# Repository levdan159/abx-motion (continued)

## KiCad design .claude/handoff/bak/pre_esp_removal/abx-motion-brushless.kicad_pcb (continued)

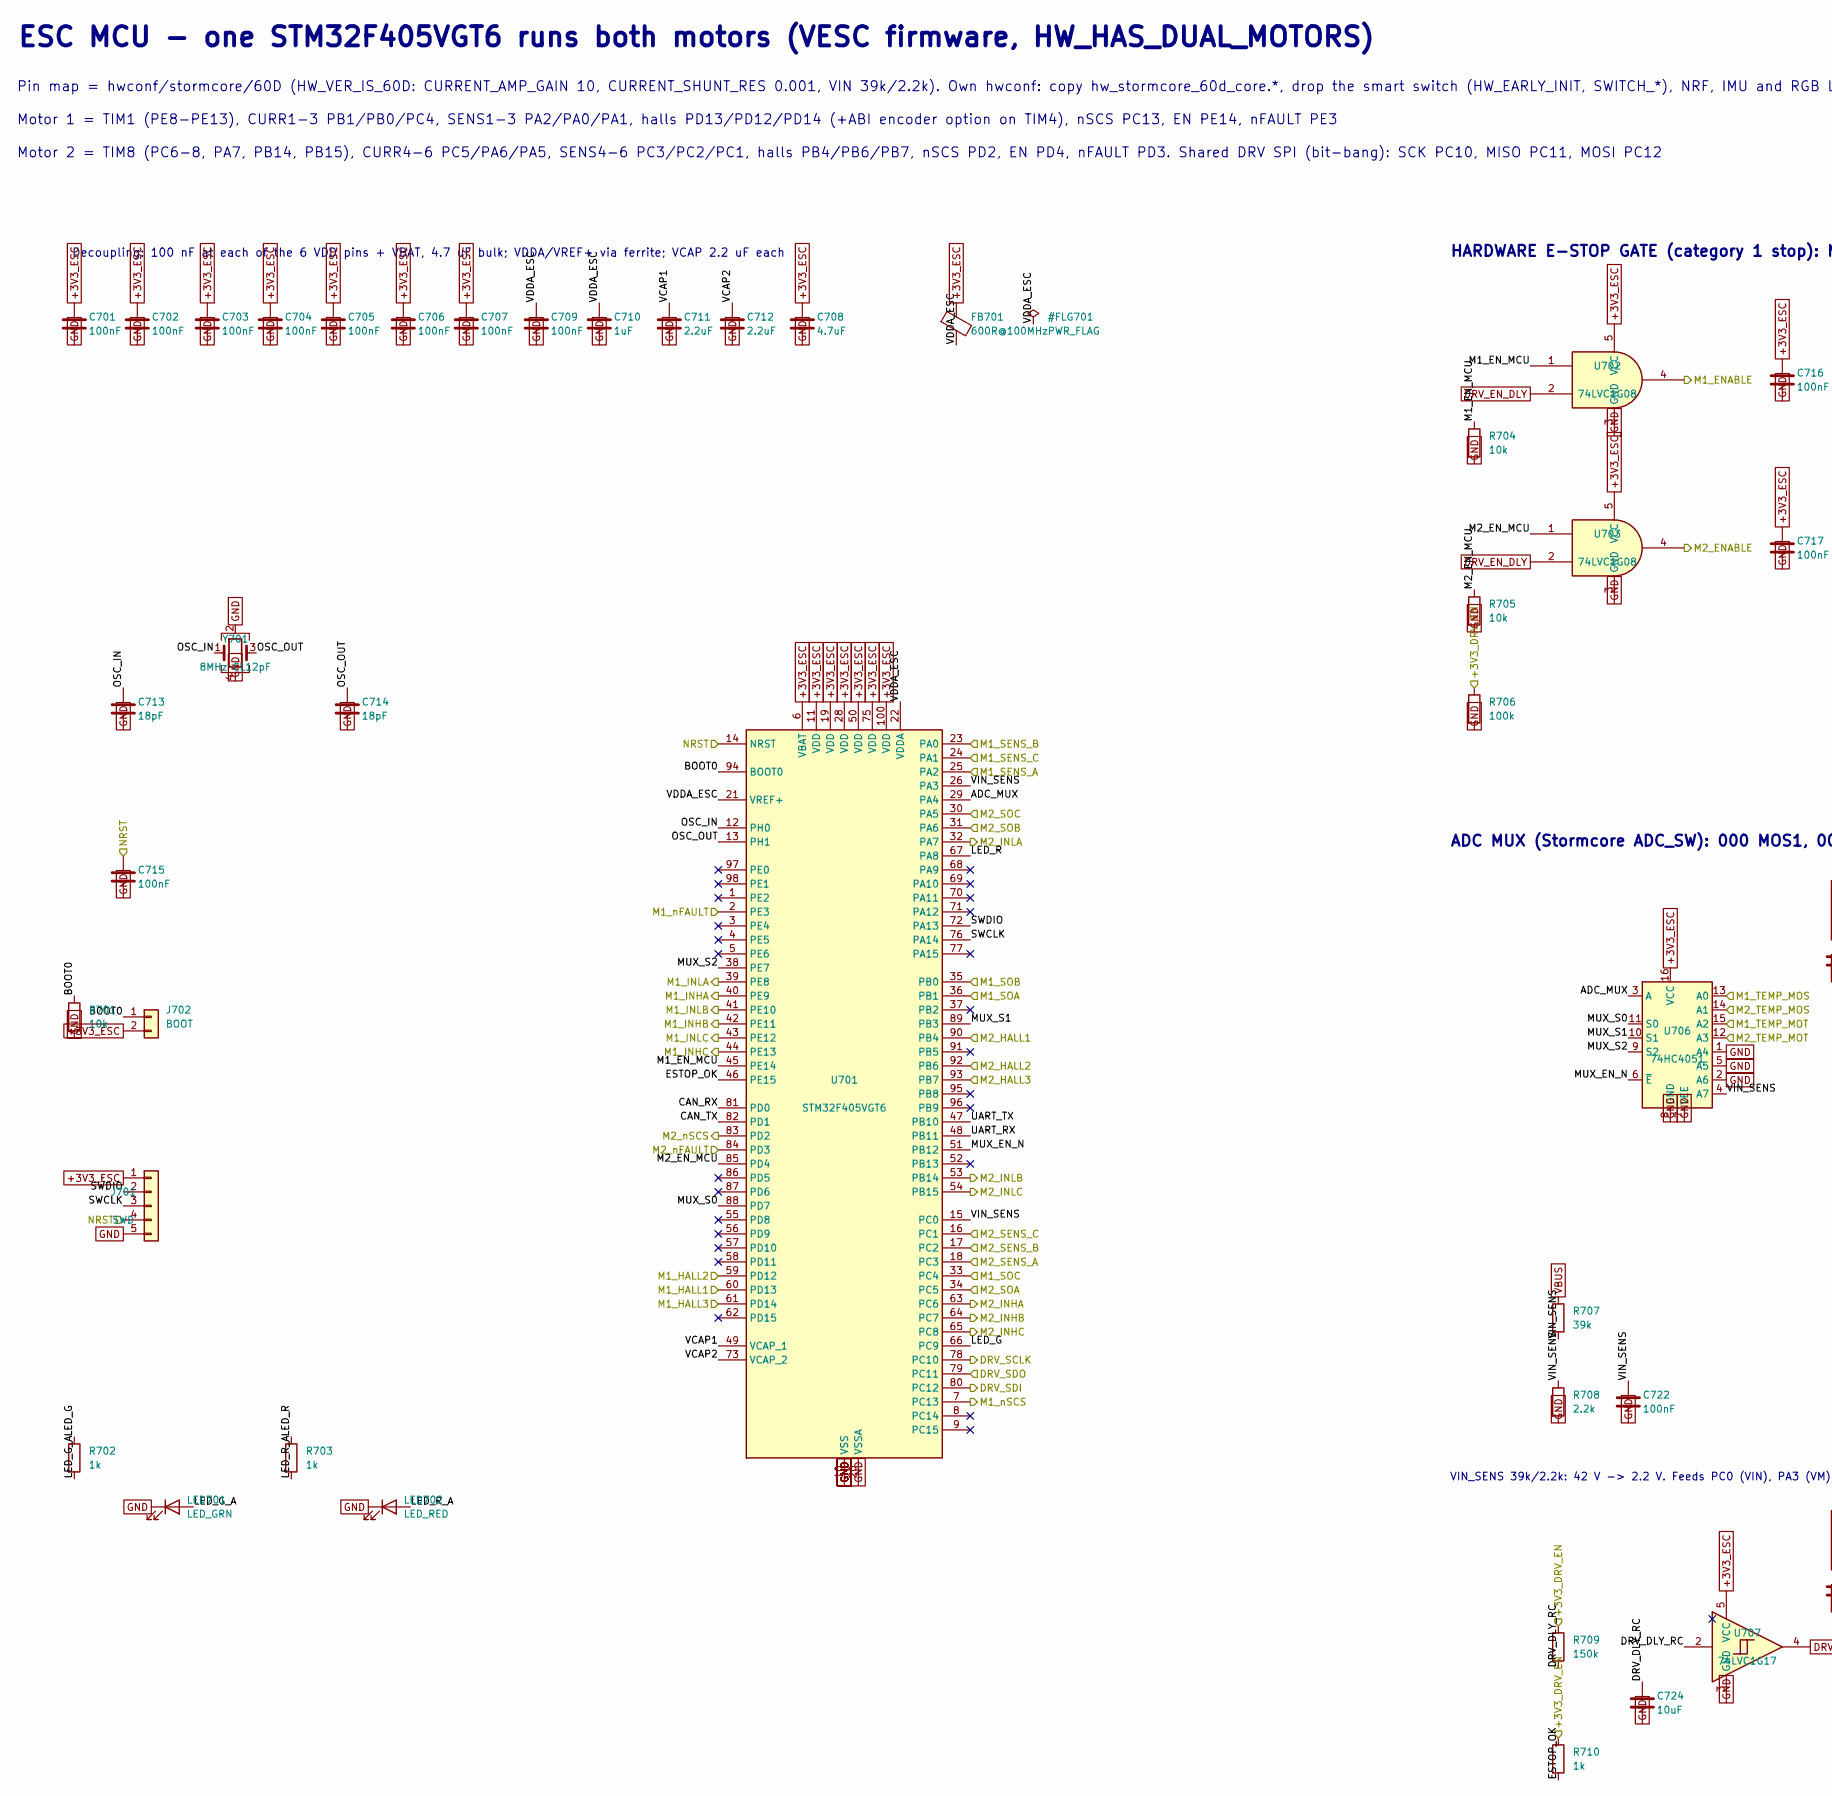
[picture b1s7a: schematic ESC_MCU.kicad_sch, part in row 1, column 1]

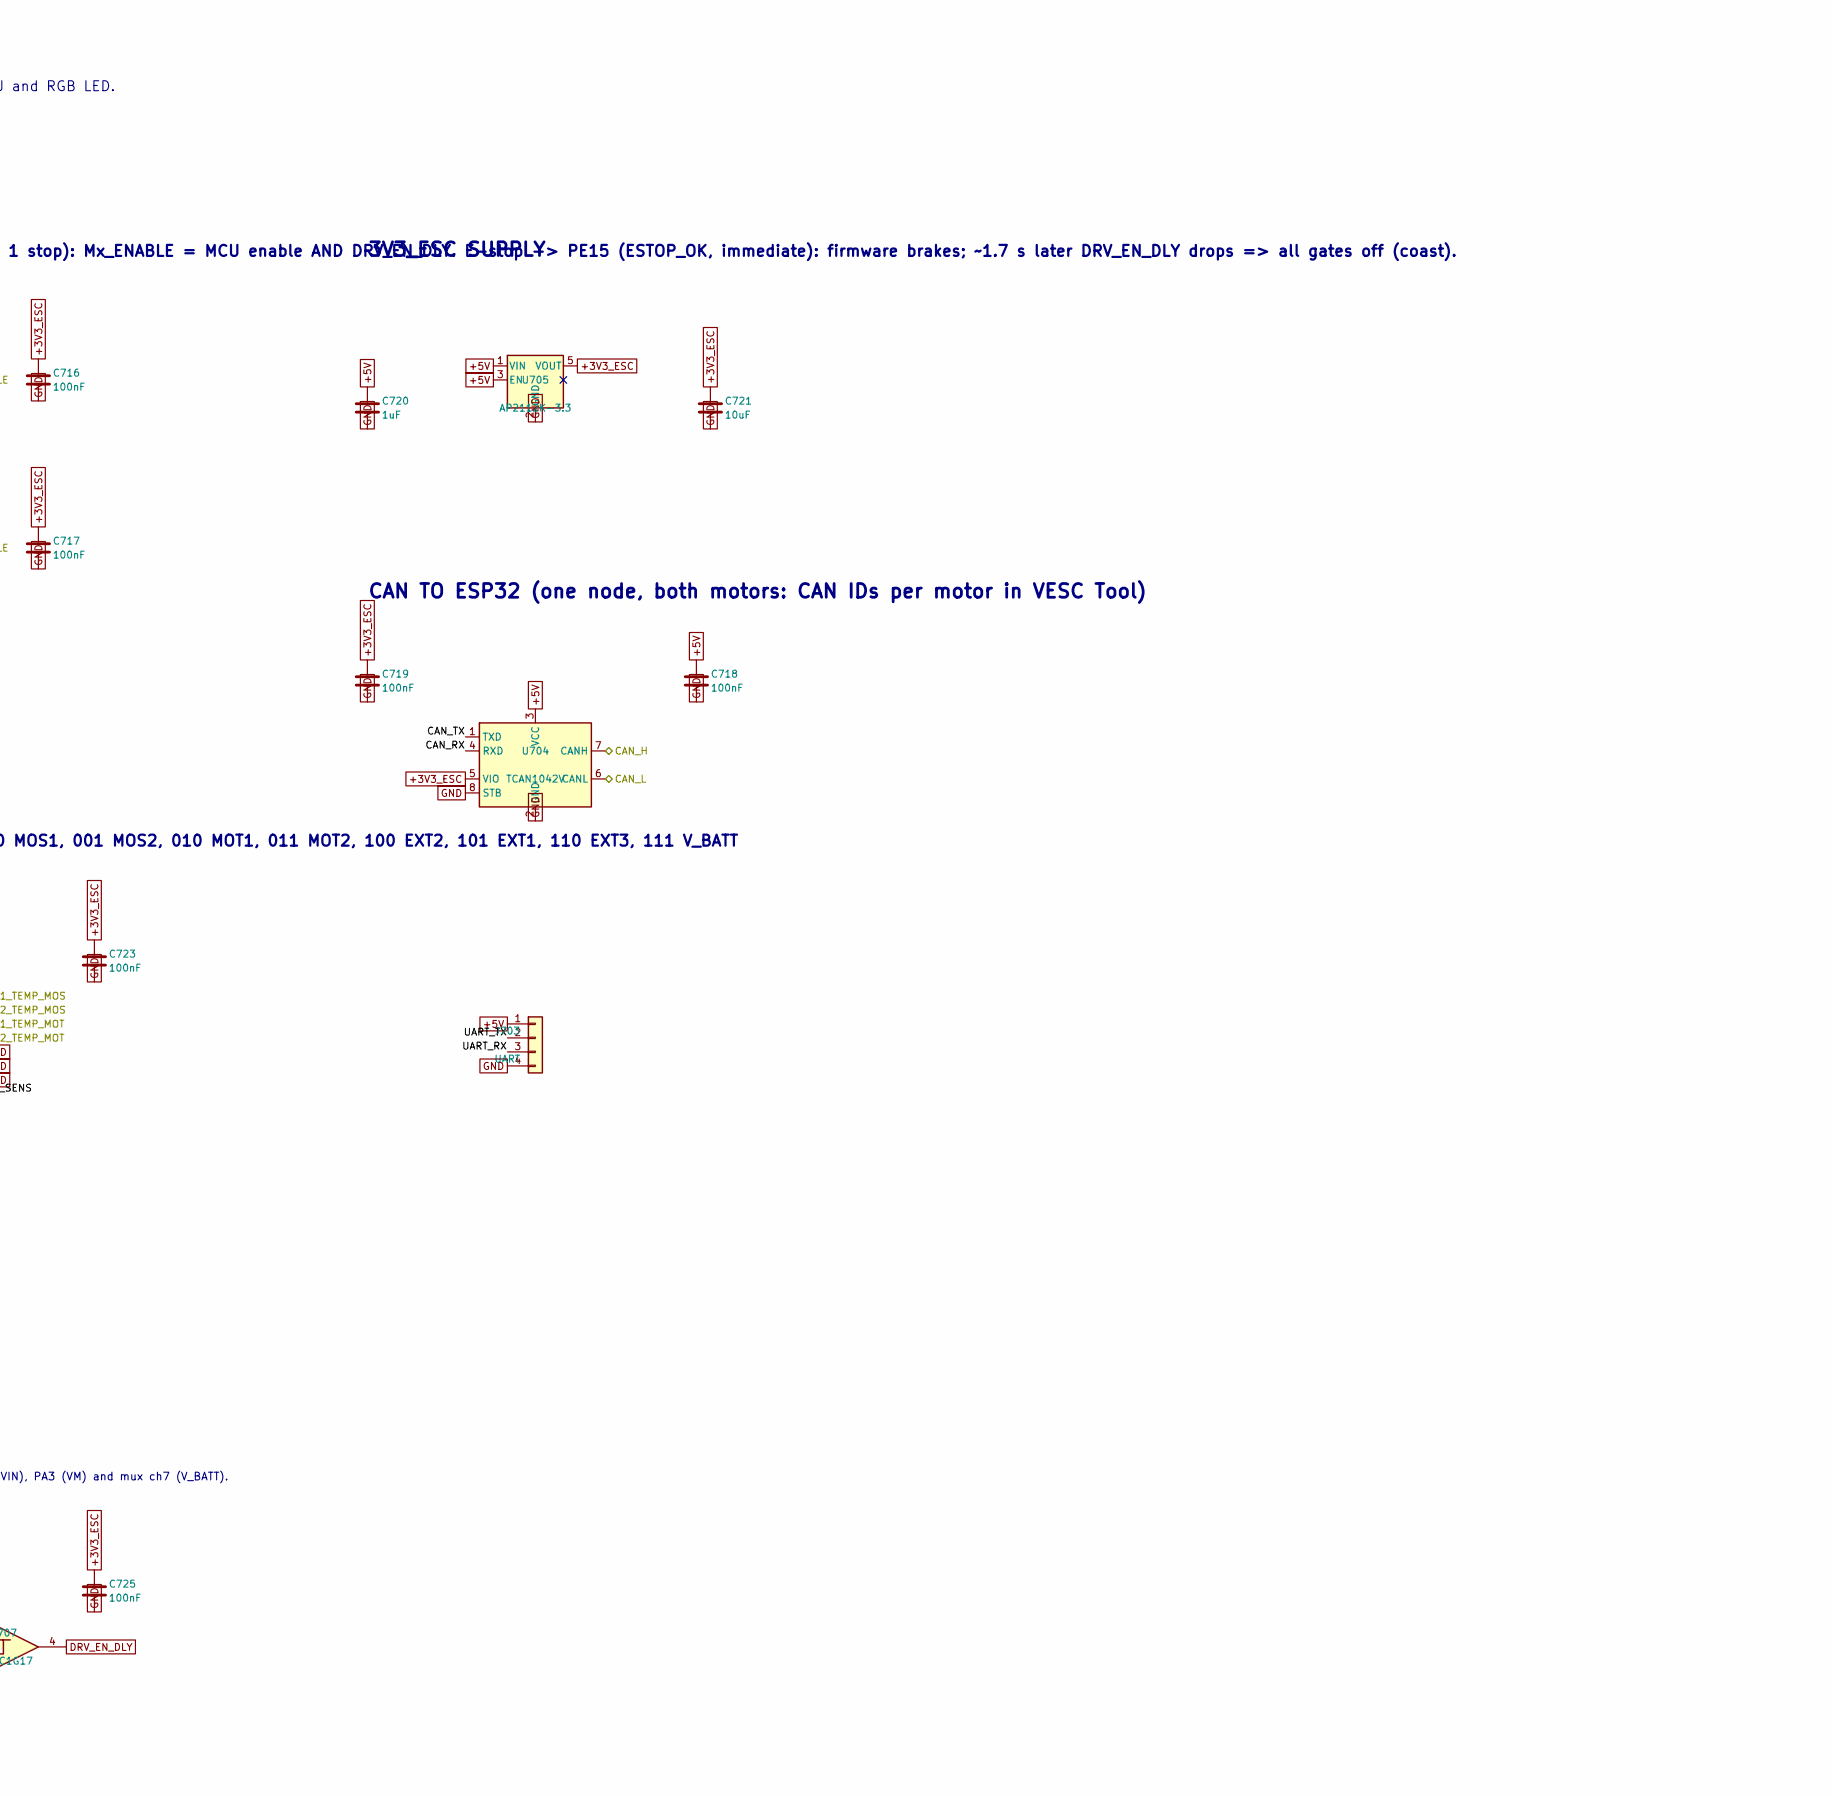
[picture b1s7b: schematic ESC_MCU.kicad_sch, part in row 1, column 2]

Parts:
C701, C702, C703, C704, C705, C706, C707, C709, C715, C716, C717, C718, C719, C722, C723, C725: 100nF; C_0603_1608Metric
C708: 4.7uF; C_0805_2012Metric
C710, C720: 1uF; C_0603_1608Metric
C711, C712: 2.2uF; C_0603_1608Metric
C713, C714: 18pF; C_0603_1608Metric
C721, C724: 10uF; C_0805_2012Metric
FB701: 600R@100MHz; L_0603_1608Metric
J701: SWD; PinHeader_1x05_P2.54mm_Vertical
J702: BOOT; PinHeader_1x02_P2.54mm_Vertical
J703: UART; JST_PH_B4B-PH-K_1x04_P2.00mm_Vertical
LED701: LED_GRN; LED_0603_1608Metric
LED702: LED_RED; LED_0603_1608Metric
R701, R704, R705: 10k; R_0603_1608Metric
R702, R703, R710: 1k; R_0603_1608Metric
R706: 100k; R_0603_1608Metric
R707: 39k; R_0805_2012Metric
R708: 2.2k; R_0603_1608Metric
R709: 150k; R_0603_1608Metric
U701: STM32F405VGT6; LQFP-100_14x14mm_P0.5mm
U702, U703: 74LVC1G08; SOT-23-5
U704: TCAN1042V; SOIC-8_3.9x4.9mm_P1.27mm
U705: AP2112K-3.3; SOT-23-5
U706: 74HC4051; TSSOP-16_4.4x5mm_P0.65mm
U707: 74LVC1G17; SOT-23-5
Y701: 8MHz CL12pF; Crystal_SMD_3225-4Pin_3.2x2.5mm

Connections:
+5V: C718.1, C720.1, J703.1, U704.3 (VCC), U705.1 (VIN), U705.3 (EN); also elsewhere on the board
/+3V3_DRV_EN: R706.1, R709.1, R710.1; also elsewhere on the board
/CAN_H: U704.7 (CANH); also elsewhere on the board
/CAN_L: U704.6 (CANL); also elsewhere on the board
/DRV_SCLK: U701.78 (PC10); also elsewhere on the board
/DRV_SDI: U701.80 (PC12); also elsewhere on the board
/DRV_SDO: U701.79 (PC11); also elsewhere on the board
/ESC_MCU/ADC_MUX: U701.29 (PA4), U706.3 (A)
/ESC_MCU/BOOT0: J702.1, R701.1, U701.94 (BOOT0)
/ESC_MCU/CAN_RX: U701.81 (PD0), U704.4 (RXD)
/ESC_MCU/CAN_TX: U701.82 (PD1), U704.1 (TXD)
/ESC_MCU/DRV_DLY_RC: C724.1, R709.2, U707.2
/ESC_MCU/ESTOP_OK: R710.2, U701.46 (PE15)
/ESC_MCU/LED_G: R702.1, U701.66 (PC9)
/ESC_MCU/LED_G_A: LED701.2 (A), R702.2
/ESC_MCU/LED_R: R703.1, U701.67 (PA8)
/ESC_MCU/LED_R_A: LED702.2 (A), R703.2
/ESC_MCU/M1_EN_MCU: R704.1, U701.45 (PE14), U702.1
/ESC_MCU/M2_EN_MCU: R705.1, U701.85 (PD4), U703.1
/ESC_MCU/MUX_EN_N: U701.51 (PB12), U706.6 (~E)
/ESC_MCU/MUX_S0: U701.88 (PD7), U706.11 (S0)
/ESC_MCU/MUX_S1: U701.89 (PB3), U706.10 (S1)
/ESC_MCU/MUX_S2: U701.38 (PE7), U706.9 (S2)
/ESC_MCU/OSC_IN: C713.1, U701.12 (PH0), Y701.1
/ESC_MCU/OSC_OUT: C714.1, U701.13 (PH1), Y701.3
/ESC_MCU/SWCLK: J701.3, U701.76 (PA14)
/ESC_MCU/SWDIO: J701.2, U701.72 (PA13)
/ESC_MCU/UART_RX: J703.3, U701.48 (PB11)
/ESC_MCU/UART_TX: J703.2, U701.47 (PB10)
/ESC_MCU/VCAP1: C711.1, U701.49 (VCAP_1)
/ESC_MCU/VCAP2: C712.1, U701.73 (VCAP_2)
/ESC_MCU/VDDA_ESC: C709.1, C710.1, FB701.2, U701.21 (VREF+), U701.22 (VDDA)
/ESC_MCU/VIN_SENS: C722.1, R707.2, R708.1, U701.15 (PC0), U701.26 (PA3), U706.4 (A7)
/ESC_NRST: C715.1, J701.4, U701.14 (NRST); also elsewhere on the board
/M1_ENABLE: U702.4; also elsewhere on the board
/M1_HALL1: U701.60 (PD13); also elsewhere on the board
/M1_HALL2: U701.59 (PD12); also elsewhere on the board
/M1_HALL3: U701.61 (PD14); also elsewhere on the board
/M1_INHA: U701.40 (PE9); also elsewhere on the board
/M1_INHB: U701.42 (PE11); also elsewhere on the board
/M1_INHC: U701.44 (PE13); also elsewhere on the board
/M1_INLA: U701.39 (PE8); also elsewhere on the board
/M1_INLB: U701.41 (PE10); also elsewhere on the board
/M1_INLC: U701.43 (PE12); also elsewhere on the board
/M1_SENS_A: U701.25 (PA2); also elsewhere on the board
/M1_SENS_B: U701.23 (PA0); also elsewhere on the board
/M1_SENS_C: U701.24 (PA1); also elsewhere on the board
/M1_SOA: U701.36 (PB1); also elsewhere on the board
/M1_SOB: U701.35 (PB0); also elsewhere on the board
/M1_SOC: U701.33 (PC4); also elsewhere on the board
/M1_TEMP_MOT: U706.15 (A2); also elsewhere on the board
/M1_nFAULT: U701.2 (PE3); also elsewhere on the board
/M1_nSCS: U701.7 (PC13); also elsewhere on the board
/M2_ENABLE: U703.4; also elsewhere on the board
/M2_HALL1: U701.90 (PB4); also elsewhere on the board
/M2_HALL2: U701.92 (PB6); also elsewhere on the board
/M2_HALL3: U701.93 (PB7); also elsewhere on the board
/M2_INHA: U701.63 (PC6); also elsewhere on the board
/M2_INHB: U701.64 (PC7); also elsewhere on the board
/M2_INHC: U701.65 (PC8); also elsewhere on the board
/M2_INLA: U701.32 (PA7); also elsewhere on the board
/M2_INLB: U701.53 (PB14); also elsewhere on the board
/M2_INLC: U701.54 (PB15); also elsewhere on the board
/M2_SENS_A: U701.18 (PC3); also elsewhere on the board
/M2_SENS_B: U701.17 (PC2); also elsewhere on the board
/M2_SENS_C: U701.16 (PC1); also elsewhere on the board
/M2_SOA: U701.34 (PC5); also elsewhere on the board
/M2_SOB: U701.31 (PA6); also elsewhere on the board
/M2_SOC: U701.30 (PA5); also elsewhere on the board
/M2_TEMP_MOS: U706.14 (A1); also elsewhere on the board
/M2_TEMP_MOT: U706.12 (A3); also elsewhere on the board
/M2_nFAULT: U701.84 (PD3); also elsewhere on the board
/M2_nSCS: U701.83 (PD2); also elsewhere on the board
DRV_EN_DLY: U702.2, U703.2, U707.4; also elsewhere on the board
VBUS: R707.1; also elsewhere on the board

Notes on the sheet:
ESC MCU - one STM32F405VGT6 runs both motors (VESC firmware, HW_HAS_DUAL_MOTORS)
Pin map = hwconf/stormcore/60D (HW_VER_IS_60D: CURRENT_AMP_GAIN 10, CURRENT_SHUNT_RES 0.001, VIN 39k/2.2k). Own hwconf: copy hw_stormcore_60d_core.*, drop the smart switch (HW_EARLY_INIT, SWITCH_*), NRF, IMU and RGB LED.
Motor 1 = TIM1 (PE8-PE13), CURR1-3 PB1/PB0/PC4, SENS1-3 PA2/PA0/PA1, halls PD13/PD12/PD14 (+ABI encoder option on TIM4), nSCS PC13, EN PE14, nFAULT PE3
Motor 2 = TIM8 (PC6-8, PA7, PB14, PB15), CURR4-6 PC5/PA6/PA5, SENS4-6 PC3/PC2/PC1, halls PB4/PB6/PB7, nSCS PD2, EN PD4, nFAULT PD3. Shared DRV SPI (bit-bang): SCK PC10, MISO PC11, MOSI PC12
Decoupling: 100 nF at each of the 6 VDD pins + VBAT, 4.7 uF bulk; VDDA/VREF+ via ferrite; VCAP 2.2 uF each
HARDWARE E-STOP GATE (category 1 stop): Mx_ENABLE = MCU enable AND DRV_EN_DLY. E-stop -> PE15 (ESTOP_OK, immediate): firmware brakes; ~1.7 s later DRV_EN_DLY drops => all gates off (coast).
ADC MUX (Stormcore ADC_SW): 000 MOS1, 001 MOS2, 010 MOT1, 011 MOT2, 100 EXT2, 101 EXT1, 110 EXT3, 111 V_BATT
VIN_SENS 39k/2.2k: 42 V -> 2.2 V. Feeds PC0 (VIN), PA3 (VM) and mux ch7 (V_BATT).
3V3_ESC SUPPLY
CAN TO ESP32 (one node, both motors: CAN IDs per motor in VESC Tool)

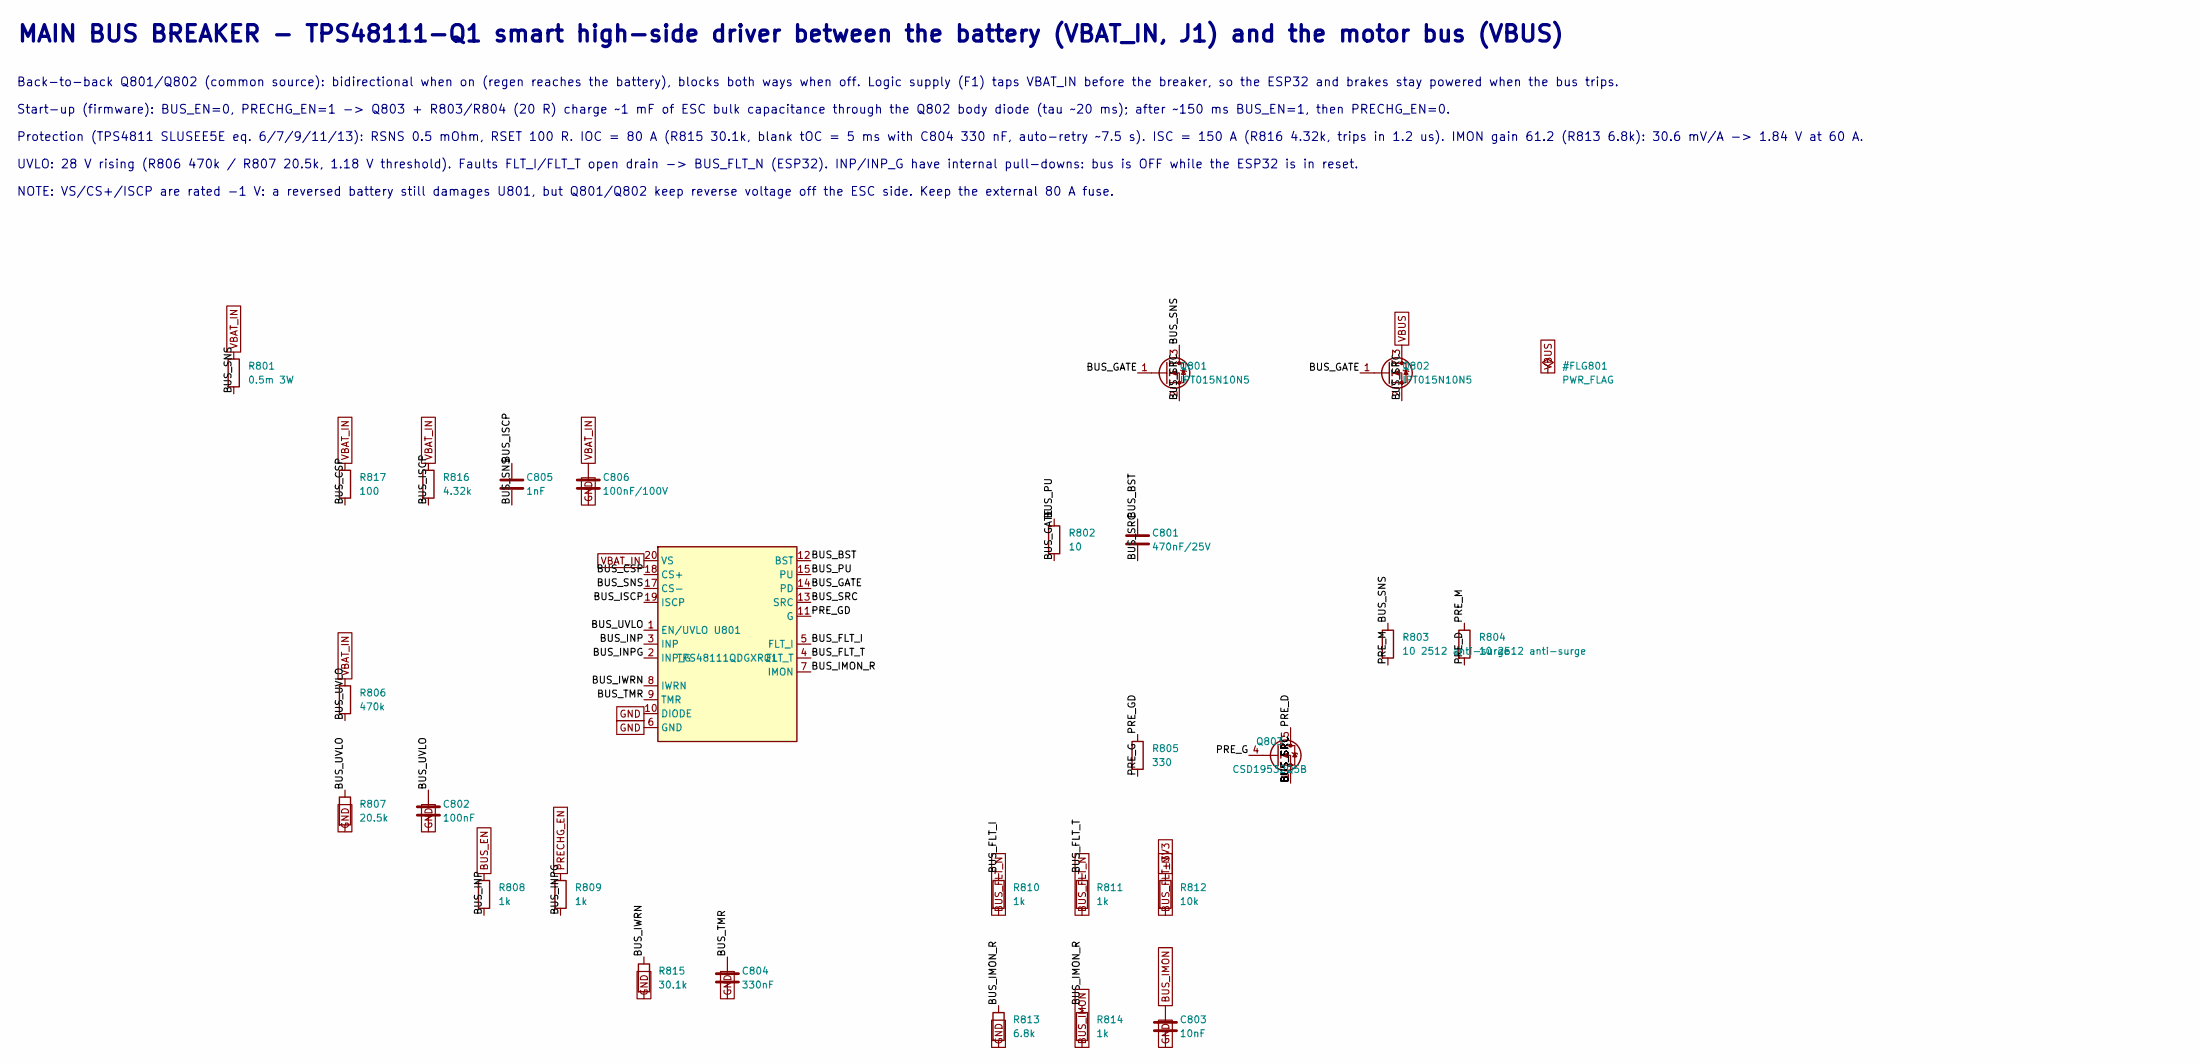
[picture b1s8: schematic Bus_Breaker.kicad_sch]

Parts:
C801: 470nF/25V; C_0603_1608Metric
C802: 100nF; C_0603_1608Metric
C803: 10nF; C_0603_1608Metric
C804: 330nF; C_0603_1608Metric
C805: 1nF; C_0603_1608Metric
C806: 100nF/100V; C_0603_1608Metric
Q801, Q802: IPT015N10N5; Infineon_PG-HSOF-8-1_ThermalVias
Q803: CSD19532Q5B; TDSON-8-1
R801: 0.5m 3W; R_2512_6332Metric
R802: 10; R_0603_1608Metric
R803, R804: 10 2512 anti-surge; R_2512_6332Metric
R805: 330; R_0603_1608Metric
R806: 470k; R_0603_1608Metric
R807: 20.5k; R_0603_1608Metric
R808, R809, R810, R811, R814: 1k; R_0603_1608Metric
R812: 10k; R_0603_1608Metric
R813: 6.8k; R_0603_1608Metric
R815: 30.1k; R_0603_1608Metric
R816: 4.32k; R_0603_1608Metric
R817: 100; R_0603_1608Metric
U801: TPS48111QDGXRQ1; TI_DGX0019A_VSSOP-19_3x5.1mm_P0.5mm

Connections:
+3V3: R812.1; also elsewhere on the board
/Bus_Breaker/BUS_BST: C801.1, U801.12 (BST)
/Bus_Breaker/BUS_CSP: R817.2, U801.18 (CS+)
/Bus_Breaker/BUS_FLT_I: R810.1, U801.5 (FLT_I)
/Bus_Breaker/BUS_FLT_T: R811.1, U801.4 (FLT_T)
/Bus_Breaker/BUS_GATE: Q801.1 (G), Q802.1 (G), R802.2, U801.14 (PD)
/Bus_Breaker/BUS_IMON_R: R813.1, R814.1, U801.7 (IMON)
/Bus_Breaker/BUS_INP: R808.2, U801.3 (INP)
/Bus_Breaker/BUS_INPG: R809.2, U801.2 (INP_G)
/Bus_Breaker/BUS_ISCP: C805.1, R816.2, U801.19 (ISCP)
/Bus_Breaker/BUS_IWRN: R815.1, U801.8 (IWRN)
/Bus_Breaker/BUS_PU: R802.1, U801.15 (PU)
/Bus_Breaker/BUS_SNS: C805.2, Q801.3 (D), R801.2, R803.1, U801.17 (CS-)
/Bus_Breaker/BUS_SRC: C801.2, Q801.2 (S), Q802.2 (S), Q803.1 (S), Q803.2 (S), Q803.3 (S), U801.13 (SRC)
/Bus_Breaker/BUS_TMR: C804.1, U801.9 (TMR)
/Bus_Breaker/BUS_UVLO: C802.1, R806.2, R807.1, U801.1 (EN/UVLO)
/Bus_Breaker/PRE_D: Q803.5 (D), R804.2
/Bus_Breaker/PRE_G: Q803.4 (G), R805.2
/Bus_Breaker/PRE_GD: R805.1, U801.11 (G)
/Bus_Breaker/PRE_M: R803.2, R804.1
BUS_EN: R808.1; also elsewhere on the board
BUS_FLT_N: R810.2, R811.2, R812.2; also elsewhere on the board
BUS_IMON: C803.1, R814.2; also elsewhere on the board
PRECHG_EN: R809.1; also elsewhere on the board
VBAT_IN: C806.1, R801.1, R806.1, R816.1, R817.1, U801.20 (VS); also elsewhere on the board
VBUS: Q802.3 (D); also elsewhere on the board

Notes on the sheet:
MAIN BUS BREAKER - TPS48111-Q1 smart high-side driver between the battery (VBAT_IN, J1) and the motor bus (VBUS)
Back-to-back Q801/Q802 (common source): bidirectional when on (regen reaches the battery), blocks both ways when off. Logic supply (F1) taps VBAT_IN before the breaker, so the ESP32 and brakes stay powered when the bus trips.
Start-up (firmware): BUS_EN=0, PRECHG_EN=1 -> Q803 + R803/R804 (20 R) charge ~1 mF of ESC bulk capacitance through the Q802 body diode (tau ~20 ms); after ~150 ms BUS_EN=1, then PRECHG_EN=0.
Protection (TPS4811 SLUSEE5E eq. 6/7/9/11/13): RSNS 0.5 mOhm, RSET 100 R. IOC = 80 A (R815 30.1k, blank tOC = 5 ms with C804 330 nF, auto-retry ~7.5 s). ISC = 150 A (R816 4.32k, trips in 1.2 us). IMON gain 61.2 (R813 6.8k): 30.6 mV/A -> 1.84 V at 60 A.
UVLO: 28 V rising (R806 470k / R807 20.5k, 1.18 V threshold). Faults FLT_I/FLT_T open drain -> BUS_FLT_N (ESP32). INP/INP_G have internal pull-downs: bus is OFF while the ESP32 is in reset.
NOTE: VS/CS+/ISCP are rated -1 V: a reversed battery still damages U801, but Q801/Q802 keep reverse voltage off the ESC side. Keep the external 80 A fuse.

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
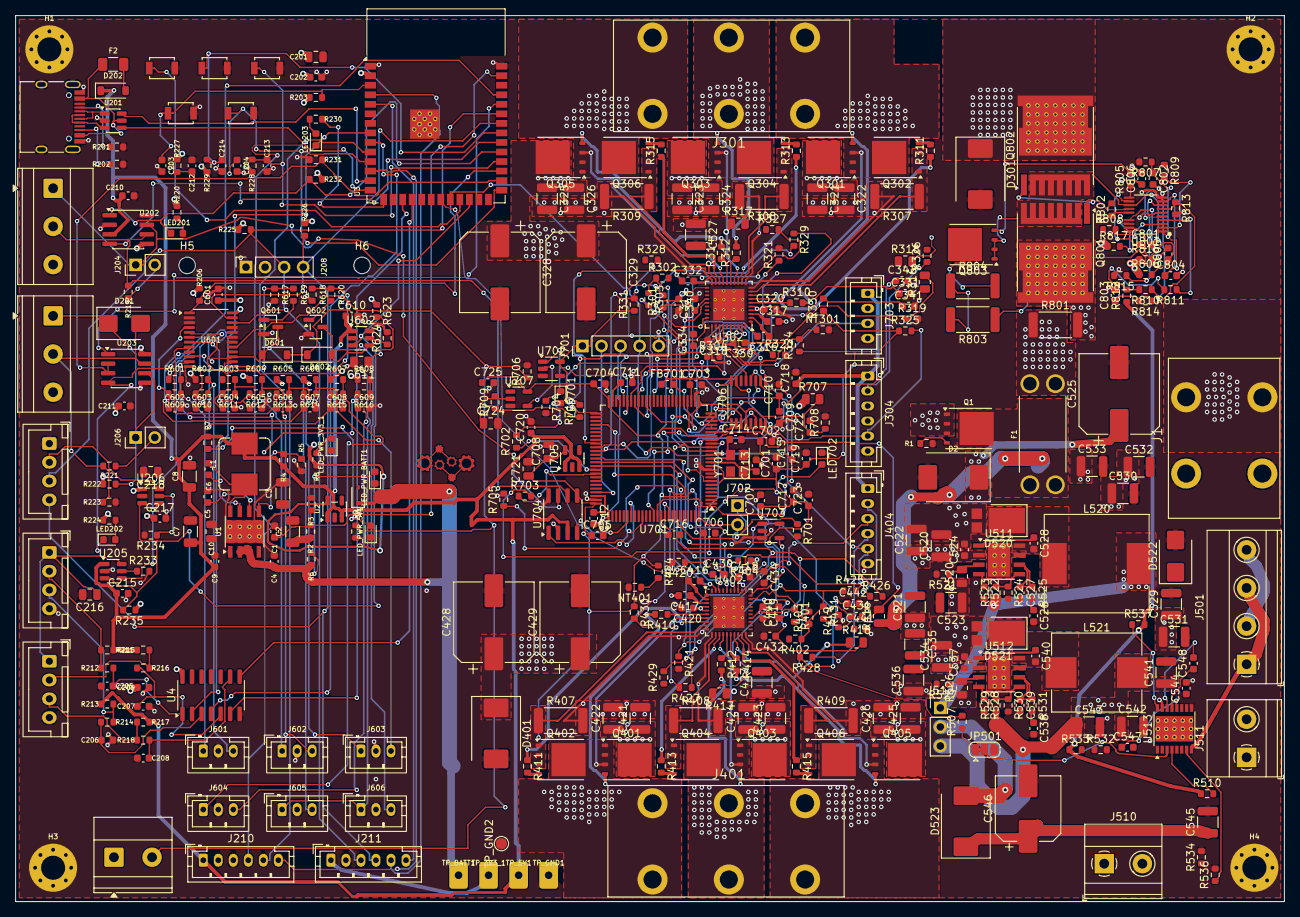
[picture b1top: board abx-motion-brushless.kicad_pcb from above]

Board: 4 copper layers, 169.0 x 118.0 mm, 421 parts (1 on the bottom side), 274 nets.

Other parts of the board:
C610: 1uF; C_0603_1608Metric
C611: 4.7uF; C_0805_2012Metric
D301, D401: SMCJ43A; D_SMC
J401: PHASES DG135T-10.16-03P; ABX_Degson_DG135T-10.16-03P
NT401: NTC 10k B3435; R_0603_1608Metric
R623: 10k; R_0603_1608Metric
R624: 470; R_0603_1608Metric
U602: MIC2009YM6; SOT-23-6

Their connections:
+3V3: R623.1; also elsewhere on the board
+5V: C610.1, U602.1 (VIN); also elsewhere on the board
/ESC_Motor_2/PH_A: J401.1; also elsewhere on the board
/ESC_Motor_2/PH_B: J401.2; also elsewhere on the board
/ESC_Motor_2/PH_C: J401.3; also elsewhere on the board
/Industrial_IO/+5V_OUT: C611.1, U602.6 (VOUT); also elsewhere on the board
/Industrial_IO/U602_ILIM: R624.1, U602.5 (ILIMIT)
/M2_TEMP_MOS: NT401.1; also elsewhere on the board
EFUSE_EN: U602.3 (EN); also elsewhere on the board
EFUSE_FLT_N: R623.2, U602.4 (FAULT); also elsewhere on the board
VBUS: D301.1 (A1), D401.1 (A1); also elsewhere on the board
